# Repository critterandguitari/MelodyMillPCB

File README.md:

# MelodyMillPCB
PCB for Melody Mill Eurorack Module

License is CC BY-SA 2.0

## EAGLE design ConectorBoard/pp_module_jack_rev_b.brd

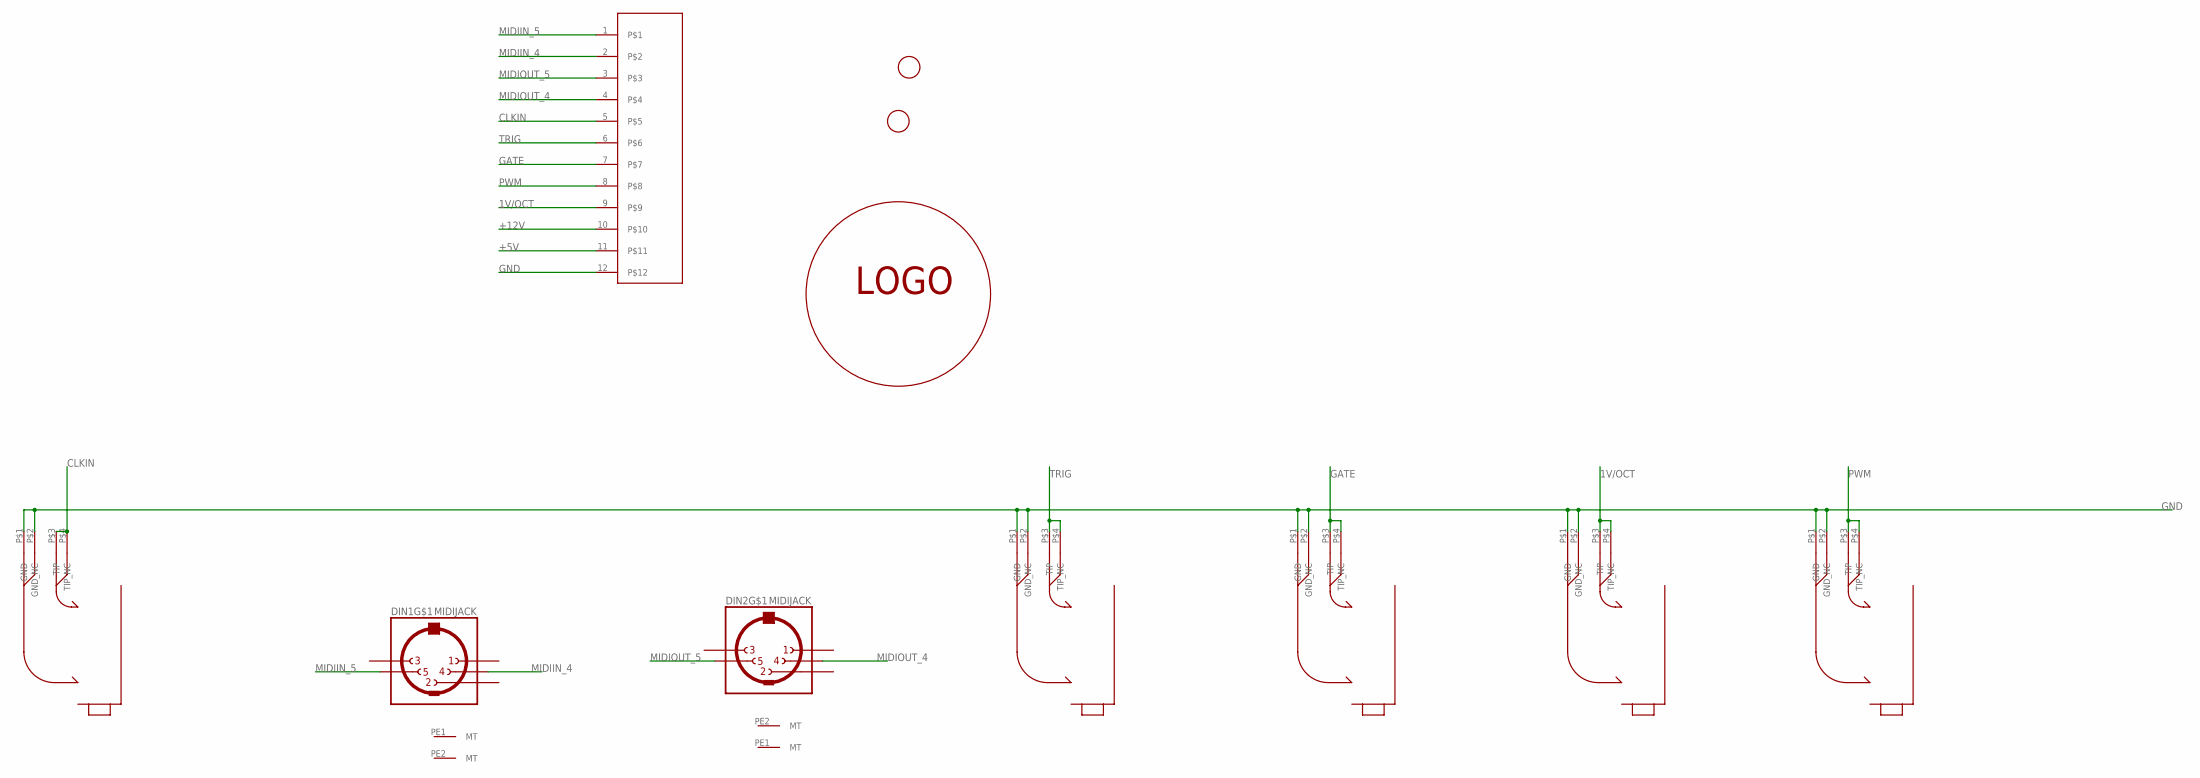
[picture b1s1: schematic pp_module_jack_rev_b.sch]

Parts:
DIN1, DIN2: MIDIJACK; CP-2350
J1, J2, J3, J4, J5: MONO_JACKCLIFF; CLIFF_JACK
SOCKET_1: CARDEDGE_12POS_SOCKET
U$1, U$2: FIDUCIAL; FIDUCIAL_1MM
U$10: LOGOCG; LOGO-CG

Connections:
1V/OCT: J4.P$3 (TIP), J4.P$4 (TIP_NC), SOCKET_1.9
+5V: SOCKET_1.11
+12V: SOCKET_1.10
CLKIN: J1.P$3 (TIP), J1.P$4 (TIP_NC), SOCKET_1.5
GATE: J3.P$3 (TIP), J3.P$4 (TIP_NC), SOCKET_1.7
GND: J1.P$1 (GND), J1.P$2 (GND_NC), J2.P$1 (GND), J2.P$2 (GND_NC), J3.P$1 (GND), J3.P$2 (GND_NC), J4.P$1 (GND), J4.P$2 (GND_NC), J5.P$1 (GND), J5.P$2 (GND_NC), SOCKET_1.12
MIDIIN_4: DIN1.4, SOCKET_1.2
MIDIIN_5: DIN1.5, SOCKET_1.1
MIDIOUT_4: DIN2.4, SOCKET_1.4
MIDIOUT_5: DIN2.5, SOCKET_1.3
PWM: J5.P$3 (TIP), J5.P$4 (TIP_NC), SOCKET_1.8
TRIG: J2.P$3 (TIP), J2.P$4 (TIP_NC), SOCKET_1.6

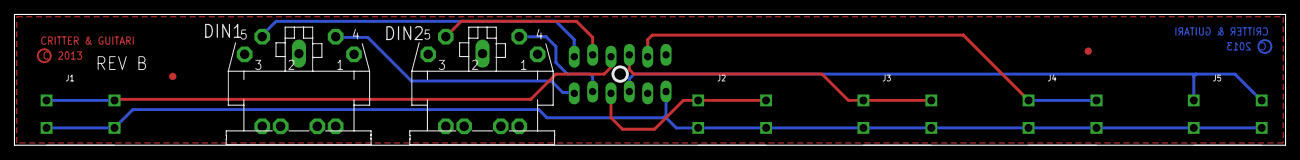
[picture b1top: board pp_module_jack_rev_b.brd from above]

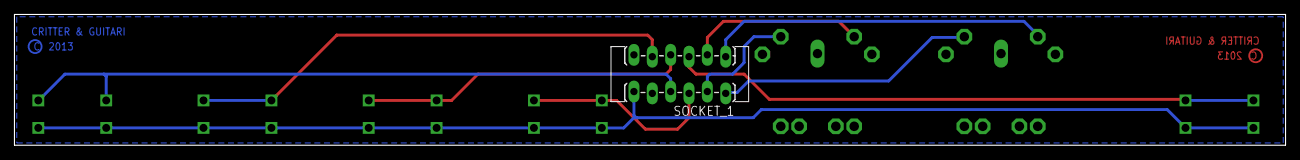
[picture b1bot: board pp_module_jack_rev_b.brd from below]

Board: 2 copper layers, 175.9 x 18.1 mm, 12 parts (2 on the bottom side), 10 nets.

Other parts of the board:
U$9: LOGOCG; LOGO-CG

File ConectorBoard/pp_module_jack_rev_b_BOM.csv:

Designator,Value,Package,Mounting,Part Number,Supplier,Qty
"DIN1, DIN2","5 P DIN JACK","PTH","PTH","CP-2350-ND	","Digikey","2"
"J2, J5, J4, J3, J1","PHONE JACK","PTH","PTH","CL1384 ","Cliff","5"
"SOCKET_1","6POS EDGECARD  ","PTH","PTH","7-5530843-6-ND	","Digikey","1"

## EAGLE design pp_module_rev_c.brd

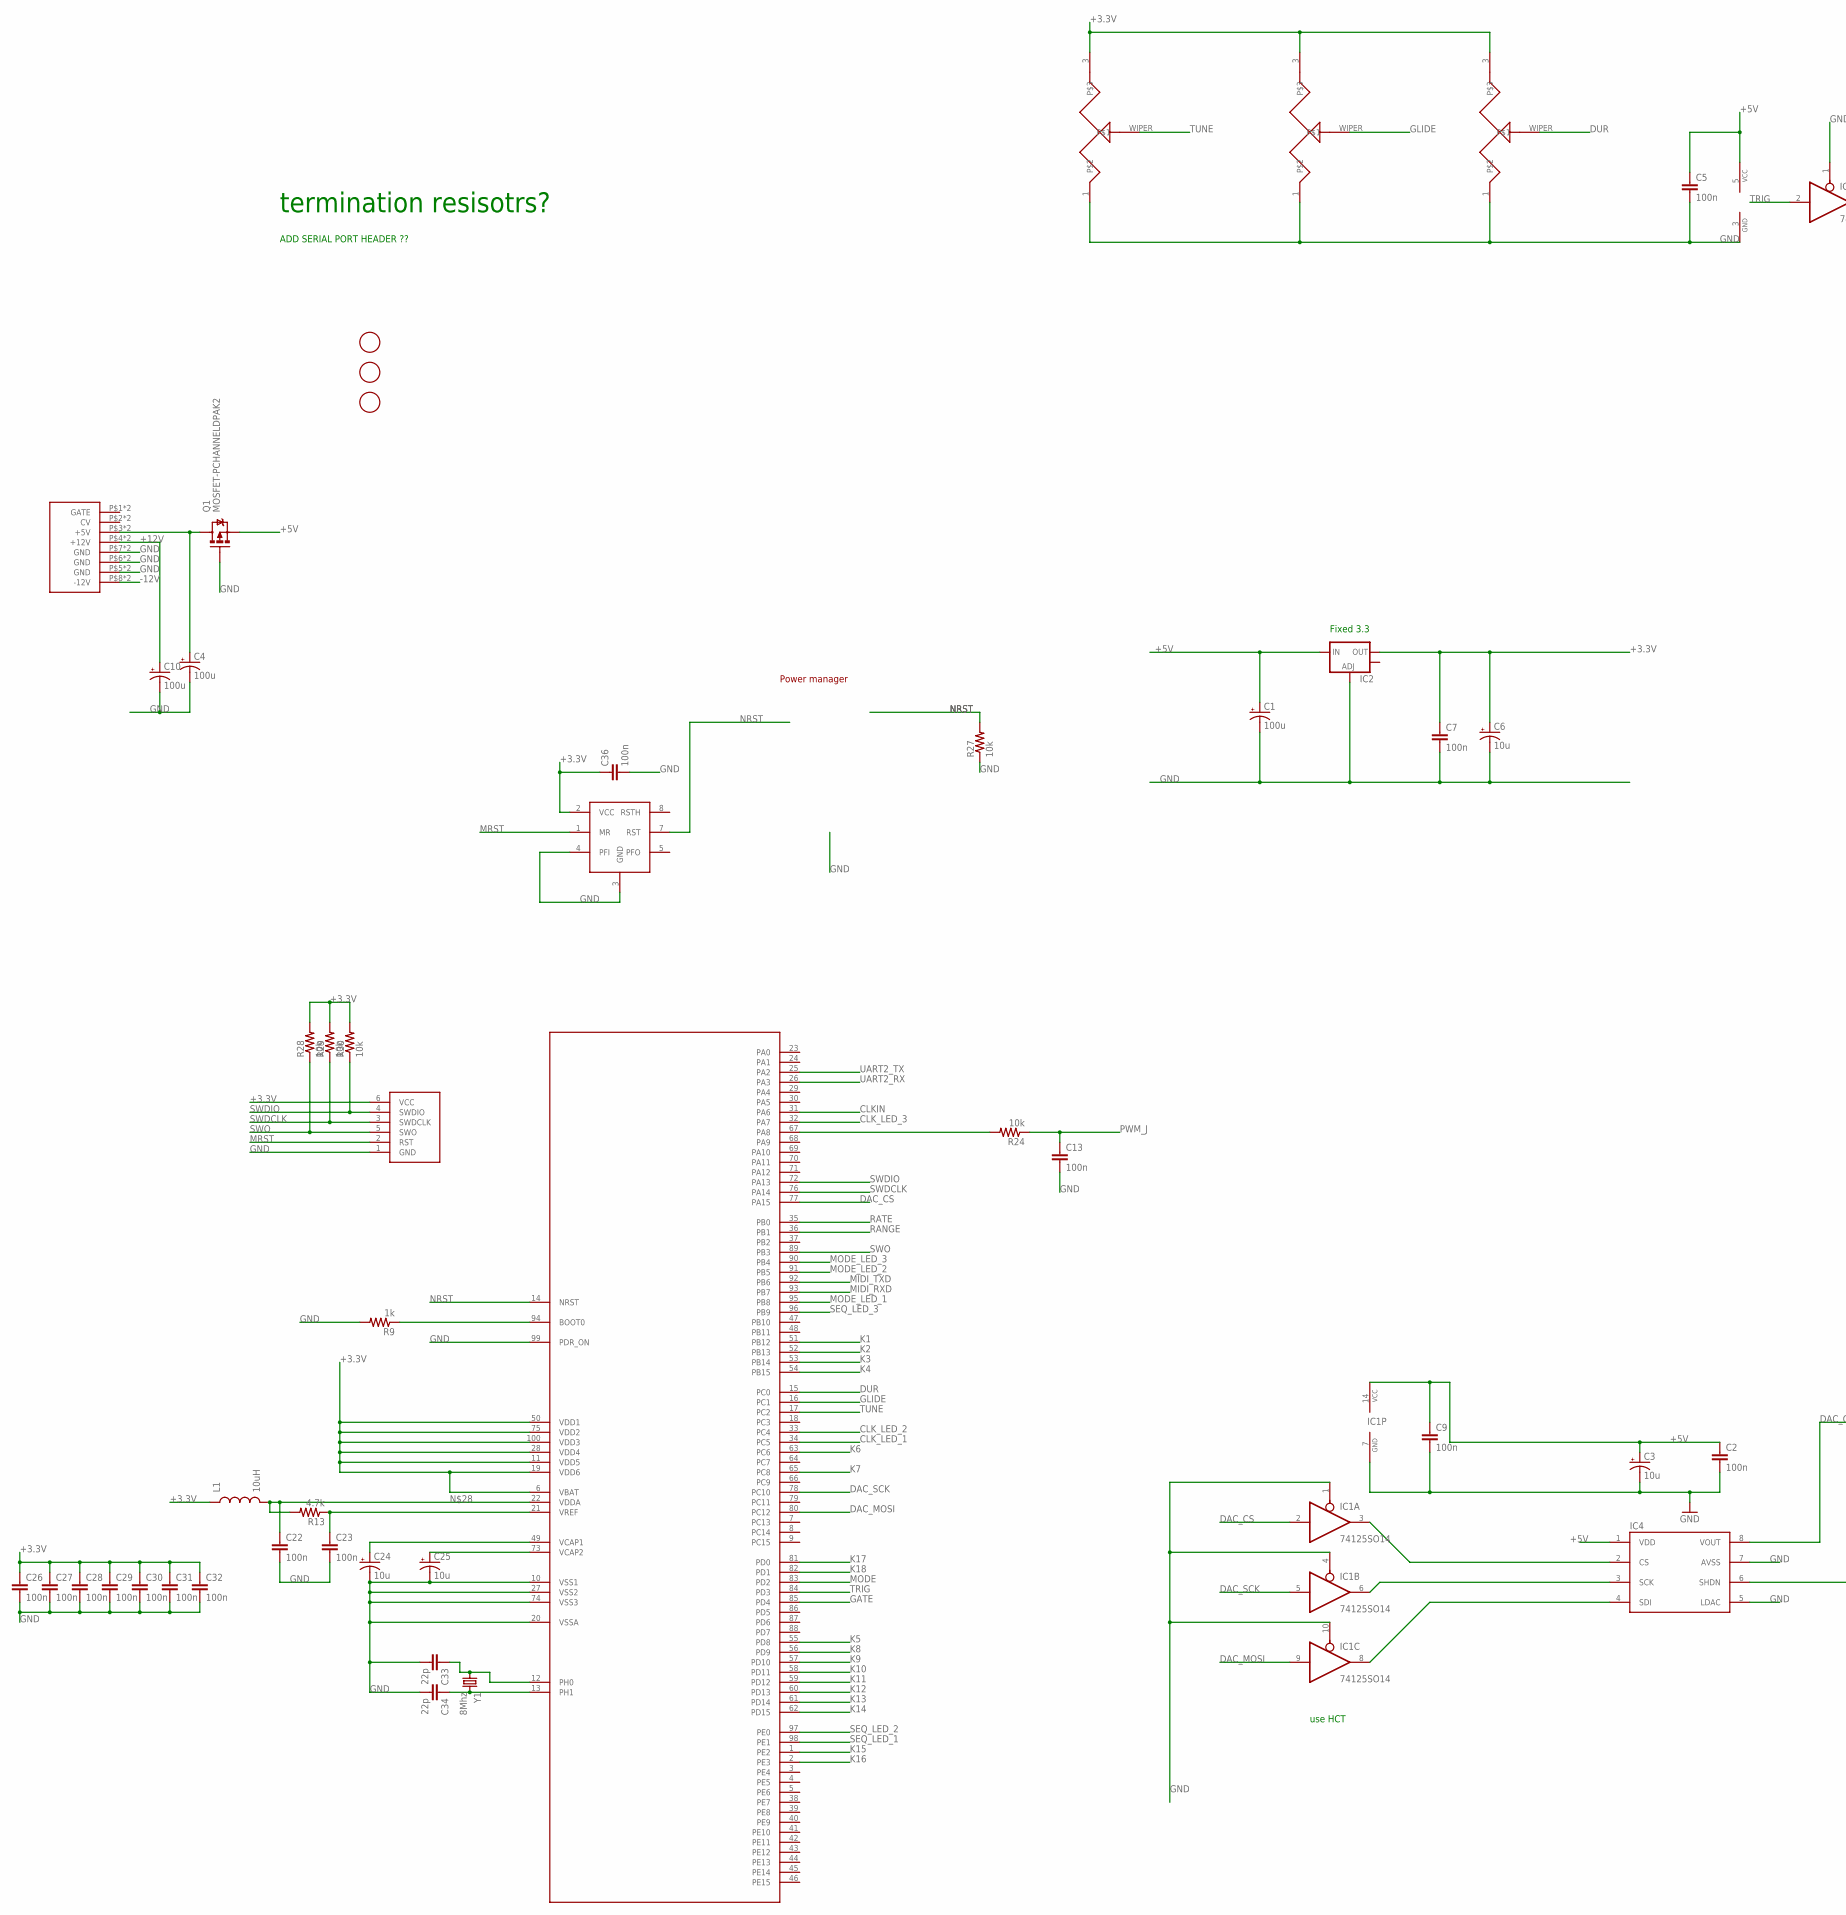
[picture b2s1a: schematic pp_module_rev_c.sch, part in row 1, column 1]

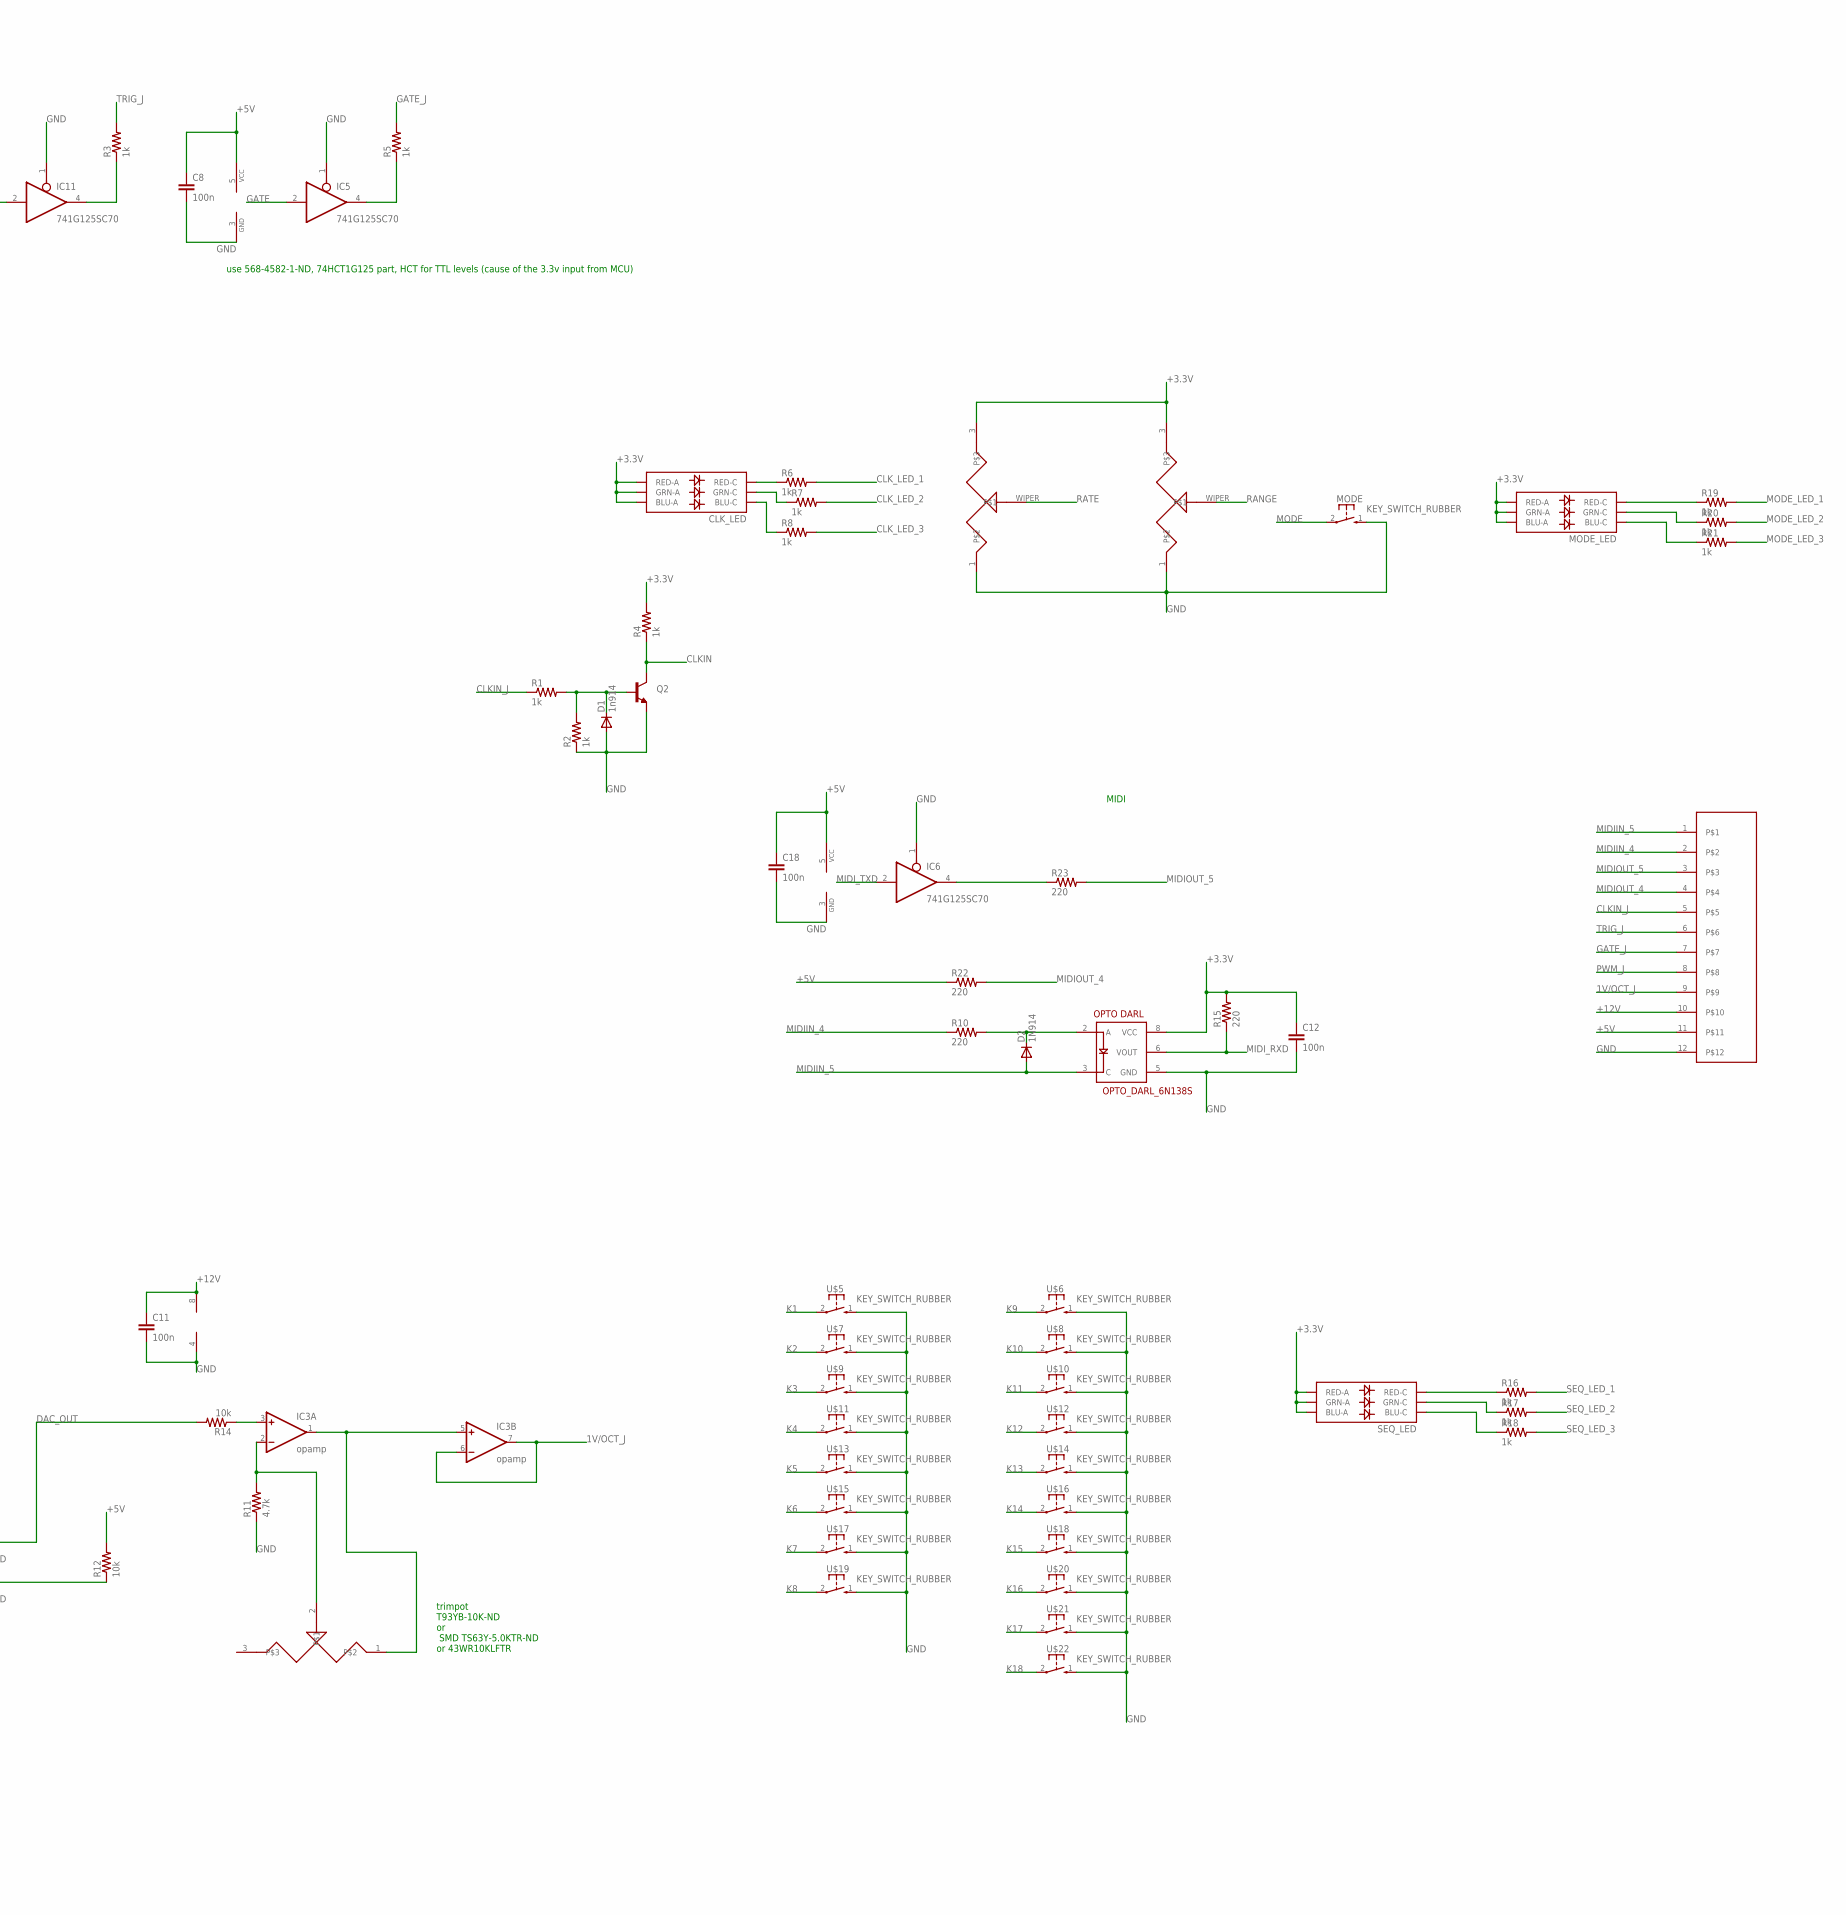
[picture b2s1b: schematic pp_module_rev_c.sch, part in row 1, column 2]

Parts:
C1, C4, C10: 100u; PANASONIC_D
C2, C5, C7, C8, C9, C11, C12, C13, C18, C22, C23, C26, C27, C28, C29, C30, C31, C32, C36: 100n; 0603-CAP
C3, C6, C24, C25: 10u; EIA3216
C33, C34: 22p; 0603-CAP
CLK_LED: LED-TRICOLOR-5050
D1: 1n914; SOD-323
D2: 1N914; SOD-323
DUR: POTVERT; POT-P09X-VERT
GLIDE: POTVERT; POT-P09X-VERT
IC1: 74125SO14; SO14
IC2: V_REG_LM1117SOT223; SOT223
IC3: opamp; SO08
IC4: MCP4821; SO08
IC5, IC6, IC11: 741G125SC70; SC-70
IC7: STM32F407VGT6; LQFP100-14X14
IC9: MAX708; SO08
L1: 10uH; 0603
MODE: KEY_SWITCH_RUBBER; KEY_CONTACT_RUBBER
MODE_LED: LED-TRICOLOR-5050
Q1: MOSFET-PCHANNELDPAK2; DPAK2
Q2: TRANSISTOR_NPNSOT23-3; SOT23-3
R1, R2, R3, R4, R5, R6, R7, R8, R9, R16, R17, R18, R19, R20, R21: 1k; 0603-RES
R10, R15, R22, R23: 220; 0603-RES
R11, R13: 4.7k; 0603-RES
R12, R14, R24, R27, R28, R29, R30: 10k; 0603-RES
RANGE: POTVERT; POT-P09X-VERT
RATE: POTVERT; POT-P09X-VERT
SEQ_LED: LED-TRICOLOR-5050
SWD: SWD6PIN; 2X3
TUNE: POTVERT; POT-P09X-VERT
U$1, U$23, U$24: FIDUCIAL; FIDUCIAL_1MM
U$2: POTSMD-TRIMMER; POT-TRIM-TT-43
U$3: CARDEDGE_12POS_MALE
U$4: OPTO_DARL_6N138S; 8-SMD
U$5, U$6, U$7, U$8, U$9, U$10, U$11, U$12, U$13, U$14, U$15, U$16, U$17, U$18, U$19, U$20, U$21, U$22: KEY_SWITCH_RUBBER; KEY_CONTACT_RUBBER
U$33: DOEPFER_16_CONNSMD; 2X8SMD
Y1: 8Mhz; CRYSTAL-SMD

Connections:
1N914: D1.1 (C), Q2.1 (B), R1.2, R2.2
1V/OCT_J: IC3.6 (-IN), IC3.7 (OUT), U$3.9
+3.3V: C6.A (+), C7.1, C12.1, C26.1, C27.1, C28.1, C29.1, C30.1, C31.1, C32.1, C36.1, CLK_LED.1 (BLU-A), CLK_LED.3 (GRN-A), CLK_LED.5 (RED-A), DUR.3, GLIDE.3, IC2.2 (OUT), IC7.6 (VBAT), IC7.11 (VDD5), IC7.19 (VDD6), IC7.28 (VDD4), IC7.50 (VDD1), IC7.75 (VDD2), IC7.100 (VDD3), IC9.2 (VCC), L1.1, MODE_LED.1 (BLU-A), MODE_LED.3 (GRN-A), MODE_LED.5 (RED-A), R4.2, R15.2, R28.2, R29.2, R30.2, RANGE.3, RATE.3, SEQ_LED.1 (BLU-A), SEQ_LED.3 (GRN-A), SEQ_LED.5 (RED-A), SWD.6 (VCC), TUNE.3, U$4.8 (VCC)
+5V: C1.+, C2.1, C3.A (+), C5.1, C8.1, C9.1, C18.1, IC1.14 (VCC), IC2.3 (IN), IC4.1 (VDD), IC5.5 (VCC), IC6.5 (VCC), IC11.5 (VCC), Q1.3 (S), R12.2, R22.1, U$3.11
+12V: C10.+, C11.1, IC3.8 (V+), U$3.10, U$33.P$4 (+12V), U$33.P$12 (+12V)
-12V: U$33.P$8 (-12V), U$33.P$16 (-12V)
CLKIN: IC7.31 (PA6), Q2.3 (C), R4.1
CLKIN_J: R1.1, U$3.5
CLK_LED_1: IC7.34 (PC5), R6.2
CLK_LED_2: IC7.33 (PC4), R7.2
CLK_LED_3: IC7.32 (PA7), R8.2
DAC_CS: IC1.2 (I), IC7.77 (PA15)
DAC_MOSI: IC1.9 (I), IC7.80 (PC12)
DAC_OUT: IC4.8 (VOUT), R14.2
DAC_SCK: IC1.5 (I), IC7.78 (PC10)
DUR: DUR.WIPER, IC7.15 (PC0)
GATE: IC5.2 (I), IC7.85 (PD4)
GATE_J: R5.2, U$3.7
GLIDE: GLIDE.WIPER, IC7.16 (PC1)
GND: C1.-, C2.2, C3.C (-), C4.-, C5.2, C6.C (-), C7.2, C8.2, C9.2, C10.-, C11.2, C12.2, C13.2, C18.2, C22.2, C23.2, C24.C (-), C25.C (-), C26.2, C27.2, C28.2, C29.2, C30.2, C31.2, C32.2, C33.2, C34.2, C36.2, D1.2 (A), DUR.1, GLIDE.1, IC1.1 (OE), IC1.4 (OE), IC1.7 (GND), IC1.10 (OE), IC2.1 (ADJ), IC3.4 (V-), IC4.5 (LDAC), IC4.7 (AVSS), IC5.1 (OE), IC5.3 (GND), IC6.1 (OE), IC6.3 (GND), IC7.10 (VSS1), IC7.20 (VSSA), IC7.27 (VSS2), IC7.74 (VSS3), IC7.99 (PDR_ON), IC9.3 (GND), IC9.4 (PFI), IC11.1 (OE), IC11.3 (GND), MODE.1 (3), Q1.1 (G), Q2.2 (E), R2.1, R9.2, R11.1, R27.1, RANGE.1, RATE.1, SWD.1 (GND), TUNE.1, U$3.12, U$4.5 (GND), U$5.1 (3), U$6.1 (3), U$7.1 (3), U$8.1 (3), U$9.1 (3), U$10.1 (3), U$11.1 (3), U$12.1 (3), U$13.1 (3), U$14.1 (3), U$15.1 (3), U$16.1 (3), U$17.1 (3), U$18.1 (3), U$19.1 (3), U$20.1 (3), U$21.1 (3), U$22.1 (3), U$33.P$5 (GND), U$33.P$6 (GND), U$33.P$7 (GND), U$33.P$13 (GND), U$33.P$14 (GND), U$33.P$15 (GND)
K1: IC7.51 (PB12), U$5.2 (1)
K2: IC7.52 (PB13), U$7.2 (1)
K3: IC7.53 (PB14), U$9.2 (1)
K4: IC7.54 (PB15), U$11.2 (1)
K5: IC7.55 (PD8), U$13.2 (1)
K6: IC7.63 (PC6), U$15.2 (1)
K7: IC7.65 (PC8), U$17.2 (1)
K8: IC7.56 (PD9), U$19.2 (1)
K9: IC7.57 (PD10), U$6.2 (1)
K10: IC7.58 (PD11), U$8.2 (1)
K11: IC7.59 (PD12), U$10.2 (1)
K12: IC7.60 (PD13), U$12.2 (1)
K13: IC7.61 (PD14), U$14.2 (1)
K14: IC7.62 (PD15), U$16.2 (1)
K15: IC7.1 (PE2), U$18.2 (1)
K16: IC7.2 (PE3), U$20.2 (1)
K17: IC7.81 (PD0), U$21.2 (1)
K18: IC7.82 (PD1), U$22.2 (1)
MIDIIN_4: R10.1, U$3.2
MIDIIN_5: D2.2 (A), U$3.1, U$4.3 (C)
MIDIOUT_4: R22.2, U$3.4
MIDIOUT_5: R23.2, U$3.3
MIDI_RXD: IC7.93 (PB7), R15.1, U$4.6 (VOUT)
MIDI_TXD: IC6.2 (I), IC7.92 (PB6)
MODE: IC7.83 (PD2), MODE.2 (1)
MODE_LED_1: IC7.95 (PB8), R19.2
MODE_LED_2: IC7.91 (PB5), R20.2
MODE_LED_3: IC7.90 (PB4), R21.2
MRST: IC9.1 (MR), SWD.2 (RST)
unnamed: MODE_LED.6 (RED-C), R19.1
unnamed: MODE_LED.4 (GRN-C), R20.1
unnamed: C34.1, IC7.13 (PH1), Y1.2
unnamed: MODE_LED.2 (BLU-C), R21.1
unnamed: C24.A (+), IC7.49 (VCAP1)
unnamed: C33.1, IC7.12 (PH0), Y1.1
unnamed: IC3.2 (-IN), R11.2, U$2.2
unnamed: IC3.3 (+IN), R14.1
unnamed: C4.+, Q1.4 (D), U$33.P$3 (+5V), U$33.P$11 (+5V)
unnamed: IC11.4 (O), R3.1
unnamed: CLK_LED.6 (RED-C), R6.1
unnamed: IC5.4 (O), R5.1
unnamed: IC7.67 (PA8), R24.2
unnamed: CLK_LED.4 (GRN-C), R7.1
unnamed: CLK_LED.2 (BLU-C), R8.1
unnamed: C25.A (+), IC7.73 (VCAP2)
unnamed: IC4.6 (SHDN), R12.1
unnamed: R18.1, SEQ_LED.2 (BLU-C)
unnamed: R17.1, SEQ_LED.4 (GRN-C)
unnamed: IC7.94 (BOOT0), R9.1
unnamed: R16.1, SEQ_LED.6 (RED-C)
unnamed: IC3.1 (OUT), IC3.5 (+IN), U$2.1
unnamed: IC1.3 (O), IC4.2 (CS)
unnamed: C22.1, IC7.22 (VDDA), L1.2, R13.2
unnamed: C23.1, IC7.21 (VREF), R13.1
unnamed: D2.1 (C), R10.2, U$4.2 (A)
unnamed: IC6.4 (O), R23.1
unnamed: IC1.6 (O), IC4.3 (SCK)
unnamed: IC1.8 (O), IC4.4 (SDI)
NRST: IC7.14 (NRST), IC9.7 (RST), R27.2
PWM_J: C13.1, R24.1, U$3.8
RANGE: IC7.36 (PB1), RANGE.WIPER
RATE: IC7.35 (PB0), RATE.WIPER
SEQ_LED_1: IC7.98 (PE1), R16.2
SEQ_LED_2: IC7.97 (PE0), R17.2
SEQ_LED_3: IC7.96 (PB9), R18.2
SWDCLK: IC7.76 (PA14), R29.1, SWD.3 (SWDCLK)
SWDIO: IC7.72 (PA13), R30.1, SWD.4 (SWDIO)
SWO: IC7.89 (PB3), R28.1, SWD.5 (SWO)
TRIG: IC7.84 (PD3), IC11.2 (I)
TRIG_J: R3.2, U$3.6
TUNE: IC7.17 (PC2), TUNE.WIPER
UART2_RX: IC7.26 (PA3)
UART2_TX: IC7.25 (PA2)

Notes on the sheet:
termination resisotrs?
Power manager
ADD SERIAL PORT HEADER ??
Fixed 3.3
use 568-4582-1-ND, 74HCT1G125 part, HCT for TTL levels (cause of the 3.3v input from MCU)
trimpot T93YB-10K-ND or SMD TS63Y-5.0KTR-ND or 43WR10KLFTR
use HCT
MIDI

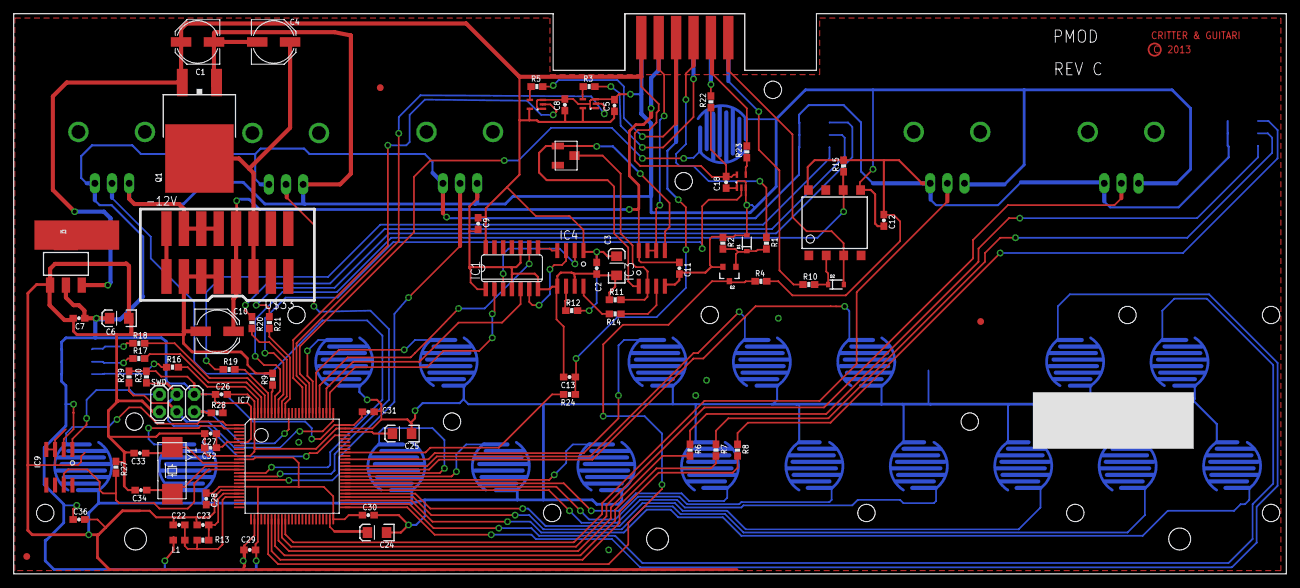
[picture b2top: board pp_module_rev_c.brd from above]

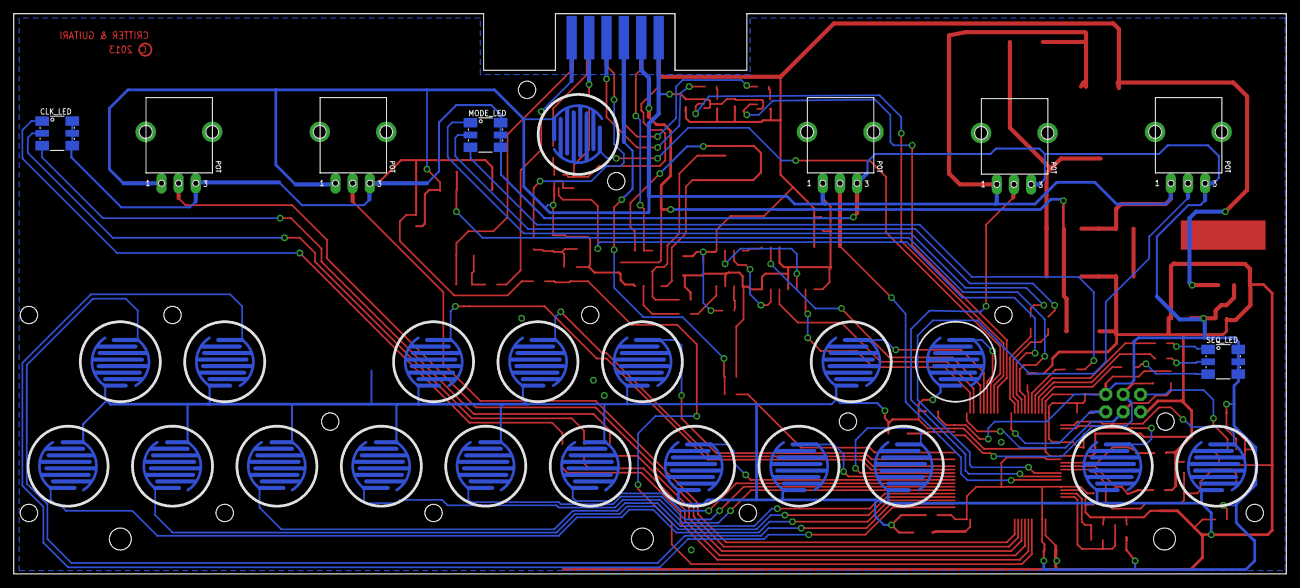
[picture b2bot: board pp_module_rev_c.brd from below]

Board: 2 copper layers, 185.7 x 81.8 mm, 107 parts (27 on the bottom side), 91 nets.

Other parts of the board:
U$25: LOGOCG; LOGO-CG

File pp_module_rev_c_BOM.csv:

Designator,Value,Package,Mounting,Part Number,Supplier,Qty
"C1, C4, C10","100uF","Panasonic D","SMT","PCE3951TR-ND","Digikey","3"
"C34, C33","22pF","0603","SMT","445-1273-2-ND","Digikey","2"
"C6, C24, C25, C3","10uF","1206","SMT","399-3687-2-ND","Digikey","4"
"C7, C27, C28, C29, C30, C22, C26, C31, C32, C23, C36, C5, C8, C9, C2, C11, C12, C18, C13",".1uF","0603","SMT","478-1239-2-ND","Digikey","19"
"D1, D2","1N914BWSTR","SOD-323","SMT","1N914BWSTR-ND","Digikey","2"
"IC1","SN74HCT125DR","14-SOIC","SMT","296-1206-2-ND","Digikey","1"
"IC11, IC5, IC6","74HCT1G125GV","SOT753","SMT","568-7746-1-ND	","Digikey","3"
"IC2","LM1117IMP-3.3","","SMT","LM1117IMP-3.3CT-ND","Digikey","1"
"IC3","LM358DRG4","8-SOIC","SMT","296-31668-1-ND	","Digikey","1"
"IC4","MCP4821","8-SOIC","SMT","MCP4821-E/SN-ND","Digikey","1"
"IC7","STM32F407VGT6","","SMT","497-12075-ND","Digikey","1"
"IC9","MAX708","","SMT","MAX708SESA-TGOSCT-ND","Digikey","1"
"L1","10uH","0603","SMT","445-3166-1-ND","Digikey","1"
"Q1","MOSFET-PCHANNEL","","SMT","FQB27P06TMCT-ND","Digikey","1"
"Q2","NPN TRANSISTOR","SOT-23","SMT","MMBT2222ATPMSCT-ND","Digikey","1"
"R10, R15, R22, R23","220","0603","SMT","P220GTR-ND ","Digikey","4"
"R13, R11","4.7K","0603","SMT","P4.7KGTR-ND","Digikey","2"
"R14","","","","","","1"
"R16, R17, R18, R19, R20, R21, R9, R6, R7, R8, R1, R2, R4","1K","0603","SMT","P1.0KGTR-ND","Digikey","13"
"R27, R28, R29, R30, R12, R24","10K","0603","SMT","        P10KGTR-ND","Digikey","6"
"R3, R5","1K","0603","SMT","P1.0KGTR-ND ","Digikey","2"
"RATE, RANGE, TUNE, DUR, GLIDE","10K","","PTH","987-1649-ND","Digikey","5"
"SEQ_LED, CLK_LED, MODE_LED","RGB LED","5050","SMT","5050-RGB","Wisdom Science &amp; Technology (HK) Co.,Ltd","3"
"U$2","10K","","SMT","987-1030-1-ND","Digikey","1"
"U$33","16 PIN HEADER","SMT-16","SMT","MSH16ETR-ND","Digikey","1"
"U$4","6N138S","8SMD","SMT","160-1798-2-ND ","Digikey","1"
"Y1","8MHz","SMT","SMT","535-10870-1-ND","Digikey","1"

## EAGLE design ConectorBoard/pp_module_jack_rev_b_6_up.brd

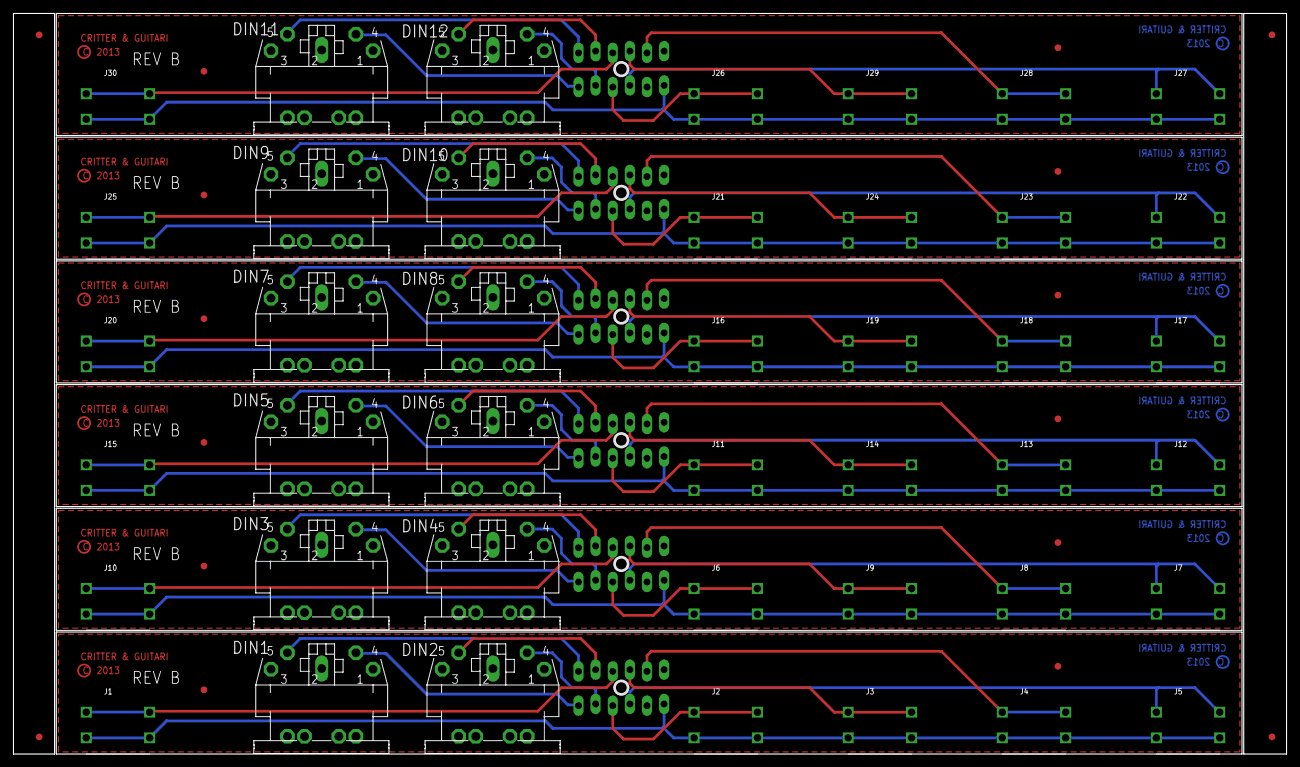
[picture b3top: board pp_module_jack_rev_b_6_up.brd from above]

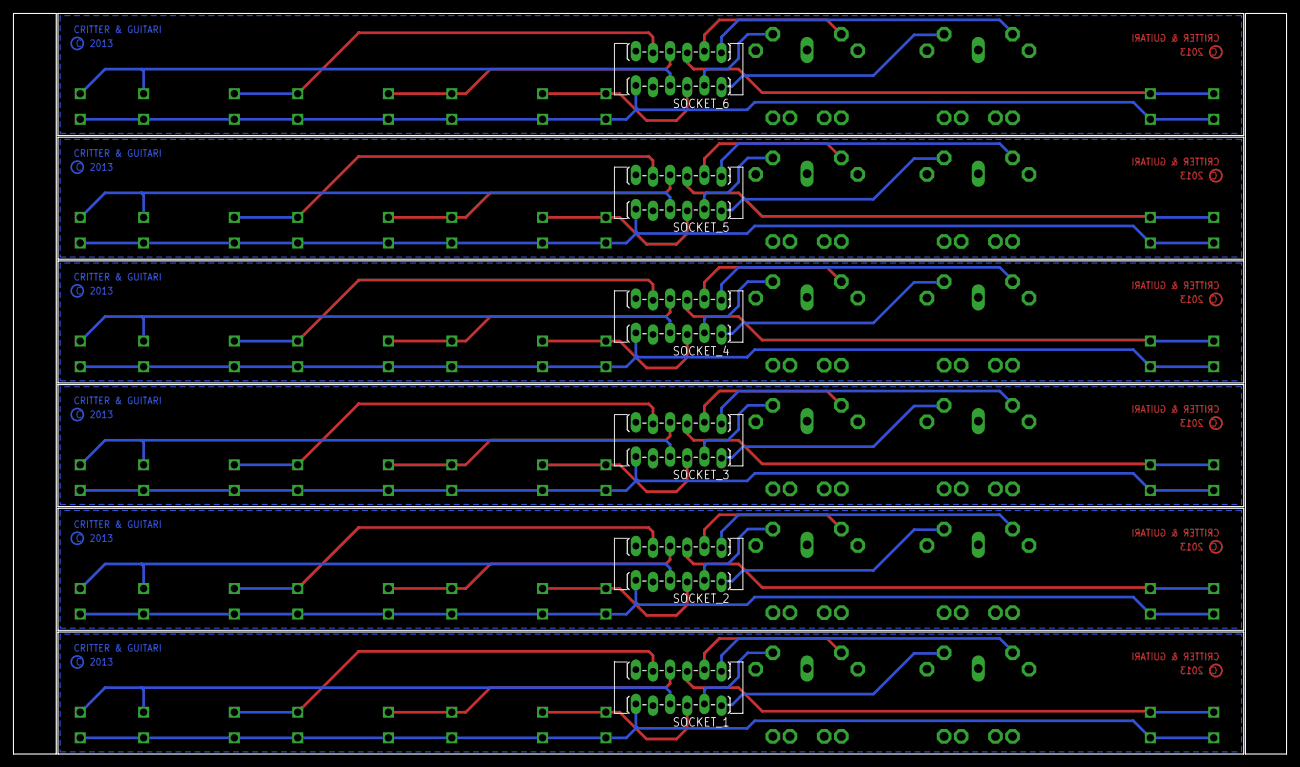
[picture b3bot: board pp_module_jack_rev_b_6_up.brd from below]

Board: 2 copper layers, 188.8 x 109.9 mm, 76 parts (12 on the bottom side), 60 nets.

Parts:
DIN1, DIN2, DIN3, DIN4, DIN5, DIN6, DIN7, DIN8, DIN9, DIN10, DIN11, DIN12: MIDIJACK; CP-2350
E$1, E$2, E$3, E$4: FIDUCIAL_1MM
J1, J2, J3, J4, J5, J6, J7, J8, J9, J10, J11, J12, J13, J14, J15, J16, J17, J18, J19, J20, J21, J22, J23, J24, J25, J26, J27, J28, J29, J30: MONO_JACKCLIFF; CLIFF_JACK
SOCKET_1, SOCKET_2, SOCKET_3, SOCKET_4, SOCKET_5, SOCKET_6: CARDEDGE_12POS_SOCKET
U$1, U$2, U$5, U$6, U$11, U$12, U$15, U$16, U$19, U$20, U$23, U$24: FIDUCIAL; FIDUCIAL_1MM
U$3, U$4, U$7, U$8, U$9, U$10, U$13, U$14, U$17, U$18, U$21, U$22: LOGOCG; LOGO-CG

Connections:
1V/OCT: J4.P$3, J4.P$4, SOCKET_1.9
1V/OCT1: J8.P$3, J8.P$4, SOCKET_2.9
1V/OCT2: J13.P$3, J13.P$4, SOCKET_3.9
1V/OCT3: J18.P$3, J18.P$4, SOCKET_4.9
1V/OCT4: J23.P$3, J23.P$4, SOCKET_5.9
1V/OCT5: J28.P$3, J28.P$4, SOCKET_6.9
CLKIN: J1.P$3, J1.P$4, SOCKET_1.5
CLKIN1: J10.P$3, J10.P$4, SOCKET_2.5
CLKIN2: J15.P$3, J15.P$4, SOCKET_3.5
CLKIN3: J20.P$3, J20.P$4, SOCKET_4.5
CLKIN4: J25.P$3, J25.P$4, SOCKET_5.5
CLKIN5: J30.P$3, J30.P$4, SOCKET_6.5
GATE: J3.P$3, J3.P$4, SOCKET_1.7
GATE1: J9.P$3, J9.P$4, SOCKET_2.7
GATE2: J14.P$3, J14.P$4, SOCKET_3.7
GATE3: J19.P$3, J19.P$4, SOCKET_4.7
GATE4: J24.P$3, J24.P$4, SOCKET_5.7
GATE5: J29.P$3, J29.P$4, SOCKET_6.7
GND: J1.P$1, J1.P$2, J2.P$1, J2.P$2, J3.P$1, J3.P$2, J4.P$1, J4.P$2, J5.P$1, J5.P$2, SOCKET_1.12
GND1: J6.P$1, J6.P$2, J7.P$1, J7.P$2, J8.P$1, J8.P$2, J9.P$1, J9.P$2, J10.P$1, J10.P$2, SOCKET_2.12
GND2: J11.P$1, J11.P$2, J12.P$1, J12.P$2, J13.P$1, J13.P$2, J14.P$1, J14.P$2, J15.P$1, J15.P$2, SOCKET_3.12
GND3: J16.P$1, J16.P$2, J17.P$1, J17.P$2, J18.P$1, J18.P$2, J19.P$1, J19.P$2, J20.P$1, J20.P$2, SOCKET_4.12
GND4: J21.P$1, J21.P$2, J22.P$1, J22.P$2, J23.P$1, J23.P$2, J24.P$1, J24.P$2, J25.P$1, J25.P$2, SOCKET_5.12
GND5: J26.P$1, J26.P$2, J27.P$1, J27.P$2, J28.P$1, J28.P$2, J29.P$1, J29.P$2, J30.P$1, J30.P$2, SOCKET_6.12
MIDIIN_1: DIN3.4, SOCKET_2.2
MIDIIN_2: DIN3.5, SOCKET_2.1
MIDIIN_3: DIN5.4, SOCKET_3.2
MIDIIN_4: DIN1.4, SOCKET_1.2
MIDIIN_5: DIN1.5, SOCKET_1.1
MIDIIN_6: DIN5.5, SOCKET_3.1
MIDIIN_7: DIN7.4, SOCKET_4.2
MIDIIN_8: DIN7.5, SOCKET_4.1
MIDIIN_9: DIN9.4, SOCKET_5.2
MIDIIN_10: DIN9.5, SOCKET_5.1
MIDIIN_11: DIN11.4, SOCKET_6.2
MIDIIN_12: DIN11.5, SOCKET_6.1
MIDIOUT_1: DIN4.5, SOCKET_2.3
MIDIOUT_2: DIN4.4, SOCKET_2.4
MIDIOUT_3: DIN6.5, SOCKET_3.3
MIDIOUT_4: DIN2.4, SOCKET_1.4
MIDIOUT_5: DIN2.5, SOCKET_1.3
MIDIOUT_6: DIN6.4, SOCKET_3.4
MIDIOUT_7: DIN8.5, SOCKET_4.3
MIDIOUT_8: DIN8.4, SOCKET_4.4
MIDIOUT_9: DIN10.5, SOCKET_5.3
MIDIOUT_10: DIN10.4, SOCKET_5.4
MIDIOUT_11: DIN12.5, SOCKET_6.3
MIDIOUT_12: DIN12.4, SOCKET_6.4
PWM: J5.P$3, J5.P$4, SOCKET_1.8
PWM1: J7.P$3, J7.P$4, SOCKET_2.8
PWM2: J12.P$3, J12.P$4, SOCKET_3.8
PWM3: J17.P$3, J17.P$4, SOCKET_4.8
PWM4: J22.P$3, J22.P$4, SOCKET_5.8
PWM5: J27.P$3, J27.P$4, SOCKET_6.8
TRIG: J2.P$3, J2.P$4, SOCKET_1.6
TRIG1: J6.P$3, J6.P$4, SOCKET_2.6
TRIG2: J11.P$3, J11.P$4, SOCKET_3.6
TRIG3: J16.P$3, J16.P$4, SOCKET_4.6
TRIG4: J21.P$3, J21.P$4, SOCKET_5.6
TRIG5: J26.P$3, J26.P$4, SOCKET_6.6
